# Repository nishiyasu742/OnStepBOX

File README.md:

# OnStepBOX

OnStepBOX is a compact, integrated controller box that combines an OnStep-compatible Smart Hand Controller (SHC) and the main OnStep controller into a single unit.  
This project is based on the **OnStep MaxESP3 hardware design** and uses the **OnStep firmware (GPLv3 licensed)**.  

---

## Overview

- **Purpose**: Simplify telescope control by merging two devices (main OnStep controller + SHC) into one.  
- **Base design**: Derived from the [OnStep MaxESP3](https://onstep.groups.io/g/main/wiki/MaxESP3) hardware.  
- **Firmware**: Fully compatible with OnStep firmware (licensed under GPLv3).  
- **Use case**: Ideal for amateur astronomers who want a reliable, compact, and user-friendly OnStep system without carrying multiple devices.  

---

## Features

- Integrated SHC and OnStep controller in a single enclosure  
- Based on the proven **OnStep MaxESP3 circuit design**  
- Compatible with the official OnStep firmware (GPLv3)    
- Compact build using an off-the-shelf plastic enclosure (machined, not 3D-printed)  
- Designed for DIY assembly with widely available components  

---

## Photos

- Image captured using a Takahashi EM200 mount.  

- OnStepBOX's appearance  

- The bottom surface of OnStepBOX  

- Inside the OnStepBOX  

---

## Schematic & Pin Mapping

This project follows the **OnStep MaxESP3** pin mapping for firmware configuration.  
Be sure to select the correct board definition in OnStep when compiling.  

- Schematic:  

---

## Required Components

- ESP32 development board (ESP-32S recommended)  
- Stepper motor drivers (e.g., DRV8825, TMC5160)  
- Standard OnStep-compatible connectors and cables  
- Off-the-shelf plastic enclosure (Takachi LC135-H-N-W)  
- Miscellaneous components (buttons, display, etc.)  

---

## Assembly Instructions

- **Prepare the enclosure**  
  Purchase the specified case (Takachi LC135-H-N-W)  and machine openings for connectors, display, and buttons using the attached G-code with a CNC milling machine.

- **Prepare the PCB**  
  Send the attached Gerber files to a PCB manufacturer (e.g., Elecrow, JLCPCB) and place an order.

- **Assemble the PCB**  
  Purchase the required components and solder them to complete the PCB.

- **Flash the firmware**  
  - Download the latest OnStep firmware.  
  - Flash the first MPU following the MaxESP3 pin map.  
  - Flash the second MPU with the Smart Hand Controller firmware.  

- **Final checks**  
  - Verify motor wiring and operation.  
  - Test the SHC interface.  
  - Confirm alignment and control with the telescope mount.  
---

## License

This project is distributed under the **GNU General Public License v3 (GPLv3)**.  
Since it is derived from **OnStep hardware and firmware**, it must remain open source.  

- A full copy of the GPLv3 license text is included in the [LICENSE](LICENSE) file.  

---

## Acknowledgments

- Original [OnStep project](https://onstep.groups.io/g/main) by **Howard Dutton** and contributors  
- OnStep MaxESP3 hardware design (the base for this project)  
- Open-source astronomy community for valuable feedback and improvements  

---

— NEWEVI

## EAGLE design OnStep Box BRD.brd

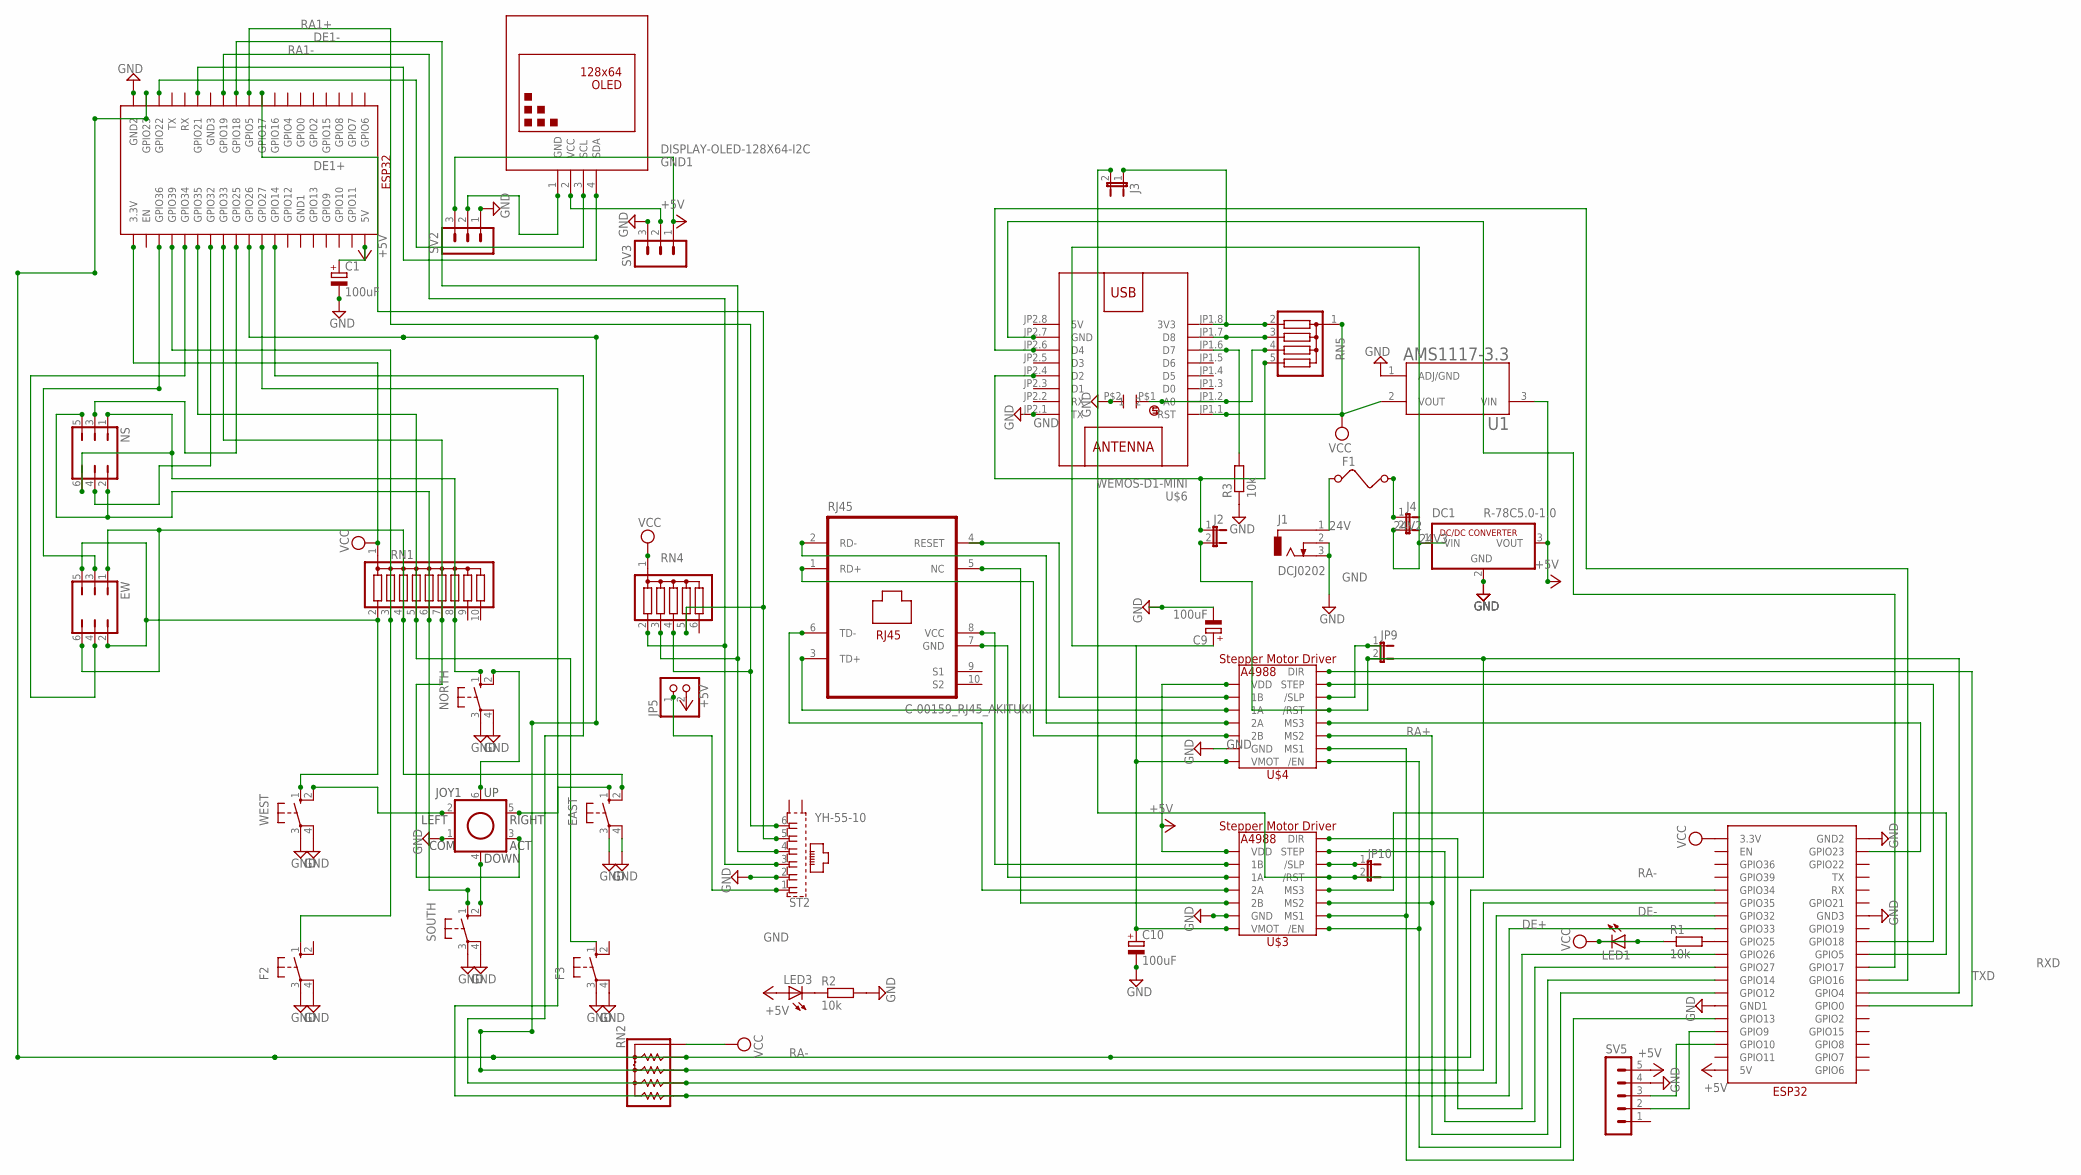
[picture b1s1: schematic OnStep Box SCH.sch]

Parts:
C1: 100uF; E2-4
C9, C10: 100uF; E2-5
CERAMIC_CAPACITOR1: CERAMIC_CAPACITOR
DC1: R-78C5.0-1.0; SIP3
EAST: 40-XX; B3F-40XX
EW: JP3Q
F1: FUSE
F2, F3: 10-XX; B3F-10XX
GND1: DISPLAY-OLED-128X64-I2C
J1: DCJ0202
J2, J3, J4: JP1E; JP1
JOY1: JOYSTICK
JP5: PINHD-1X2; 1X02
JP9, JP10: JP1E; JP1
LED1, LED3: LEDSFH480; SFH480
NORTH: 40-XX; B3F-40XX
NS: JP3Q
R1, R2, R3: 10k; 0204/5
RJ45: C-00159_RJ45_AKITUKI; PJ-J0
RN1: G09R; SIL10
RN2: 4605X; SIP5
RN4: G05R; SIL6
RN5: G04R; SIL5
SOUTH: 40-XX; B3F-40XX
ST2: YH-55-10
SV2, SV3: MA03-1
SV5: MA05-1
U1: AMS1117-3.3; SOT229P700X180-4N
U$1, U$7: ESP32
U$3, U$4: A4988_STEP
U$6: WEMOS-D1-MINI
WEST: 40-XX; B3F-40XX

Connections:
5V: U$6.JP2.8 (5V)
24V: F1.1, J1.1
24V2: F1.2, J4.1
24V3: C9.+, C10.+, DC1.1 (VIN), J4.2, U$3.VMOT, U$4.VMOT
+5V: C1.+, DC1.3 (VOUT), JP5.2, LED3.A, SV2.3, SV3.1, SV5.5, U1.3 (VIN), U$1.5V, U$3.VDD, U$4.VDD, U$7.5V
DE1+: RN4.5, ST2.5, U$7.GPIO17
DE1-: RN4.3, ST2.4, U$7.GPIO18
DE+: RN2.5, U$1.GPIO33, U$7.GPIO27
DE-: RN2.4, U$1.GPIO32, U$7.GPIO14
GND: C1.-, C9.-, C10.-, CERAMIC_CAPACITOR1.P$2 (2), DC1.2 (GND), EAST.3, EAST.4 (P1), F2.3, F2.4 (P1), F3.3, F3.4 (P1), J1.2, J1.3, JOY1.1 (COM), NORTH.3, NORTH.4 (P1), R2.2, R3.1, SOUTH.3, SOUTH.4 (P1), ST2.2, SV2.1, SV3.3, SV5.4, U1.1 (ADJ/GND), U$1.GND1, U$1.GND2, U$1.GND3, U$3.GND, U$3.GND2 (GND), U$4.GND, U$4.GND2 (GND), U$6.JP2.1 (TX), U$7.GND2, WEST.3, WEST.4 (P1)
unnamed: GND1.1 (GND), SV2.2
unnamed: LED3.K (C), R2.1
unnamed: R1.2, U$1.GPIO25
unnamed: SV5.3, U$1.GPIO10
unnamed: SV5.2, U$1.GPIO9
unnamed: U$1.GPIO12, U$3./EN, U$4./EN
unnamed: U$1.GPIO13, U$3.MS1, U$4.MS1
unnamed: U$1.GPIO14, U$3.MS2, U$4.MS2
unnamed: JP10.1, U$3./SLP
unnamed: U$1.GPIO26, U$3.DIR
unnamed: U$1.GPIO27, U$3.STEP
unnamed: U$1.GPIO23, U$4.MS3
unnamed: J2.2, J3.2, JP9.1, JP9.2, JP10.2, U$1.GPIO4, U$3./RST, U$4./RST, U$4./SLP
unnamed: J3.1, RN5.2, U$6.JP1.8 (3V3)
unnamed: U$1.GPIO18, U$4.STEP
unnamed: RJ45.4 (RESET), U$4.1B
unnamed: RJ45.5 (NC), U$3.2B
unnamed: RJ45.8 (VCC), U$3.1B
unnamed: GND1.2 (VCC), SV3.2
unnamed: RJ45.7 (GND), U$3.1A
unnamed: RN5.3, U$6.JP1.7 (D8)
unnamed: RJ45.6 (TD-), U$3.2A
unnamed: U$1.GPIO5, U$3.MS3
unnamed: R3.2, U$6.JP1.6 (D7)
unnamed: CERAMIC_CAPACITOR1.P$1 (1), RN5.4, U$6.JP1.2 (A0)
unnamed: U$1.GPIO0, U$4.DIR
unnamed: RJ45.2 (RD-), U$4.2A
unnamed: RJ45.1 (RD+), U$4.2B
unnamed: J2.1, RN5.5, U$6.JP2.4 (D2)
unnamed: RJ45.3 (TD+), U$4.1A
unnamed: GND1.3 (SCL), U$7.GPIO22
unnamed: GND1.4 (SDA), U$7.GPIO21
unnamed: EW.3, U$7.GPIO36
unnamed: EAST.2 (S1), EW.1, EW.6, RN1.4
unnamed: NS.2, NS.5, RN1.6, SOUTH.1 (S)
unnamed: JOY1.2 (LEFT), WEST.2 (S1)
unnamed: EAST.1 (S), JOY1.5 (RIGHT)
unnamed: NORTH.1 (S), NS.1, NS.6, RN1.8
unnamed: JP5.1, ST2.1
unnamed: F2.1 (S), RN1.3, U$7.GPIO39
unnamed: F3.1 (S), RN1.5, U$7.GPIO35
unnamed: NS.3, U$7.GPIO25
unnamed: NS.4, U$7.GPIO32
unnamed: EW.2, EW.5, RN1.2, WEST.1 (S)
unnamed: EW.4, U$7.GPIO34
unnamed: JOY1.6 (UP), NORTH.2 (S1)
unnamed: JOY1.4 (DOWN), SOUTH.2 (S1)
unnamed: JOY1.3 (ACT), RN1.7, U$7.GPIO33
RA1+: RN4.4, ST2.6, U$7.GPIO5
RA1-: RN4.2, ST2.3, U$7.GPIO19
RA+: RN2.3, U$1.GPIO35, U$7.GPIO26
RA-: RN2.2, U$1.GPIO34, U$7.GPIO23
RXD: U$1.GPIO17, U$6.JP2.7 (GND)
TXD: U$1.GPIO16, U$6.JP2.6 (D4)
VCC: LED1.A, LED1.K (C), R1.1, RN1.1, RN2.1, RN4.1, RN5.1, U1.2 (VOUT), U$1.3.3V, U$6.JP1.1 (RST), U$7.3.3V

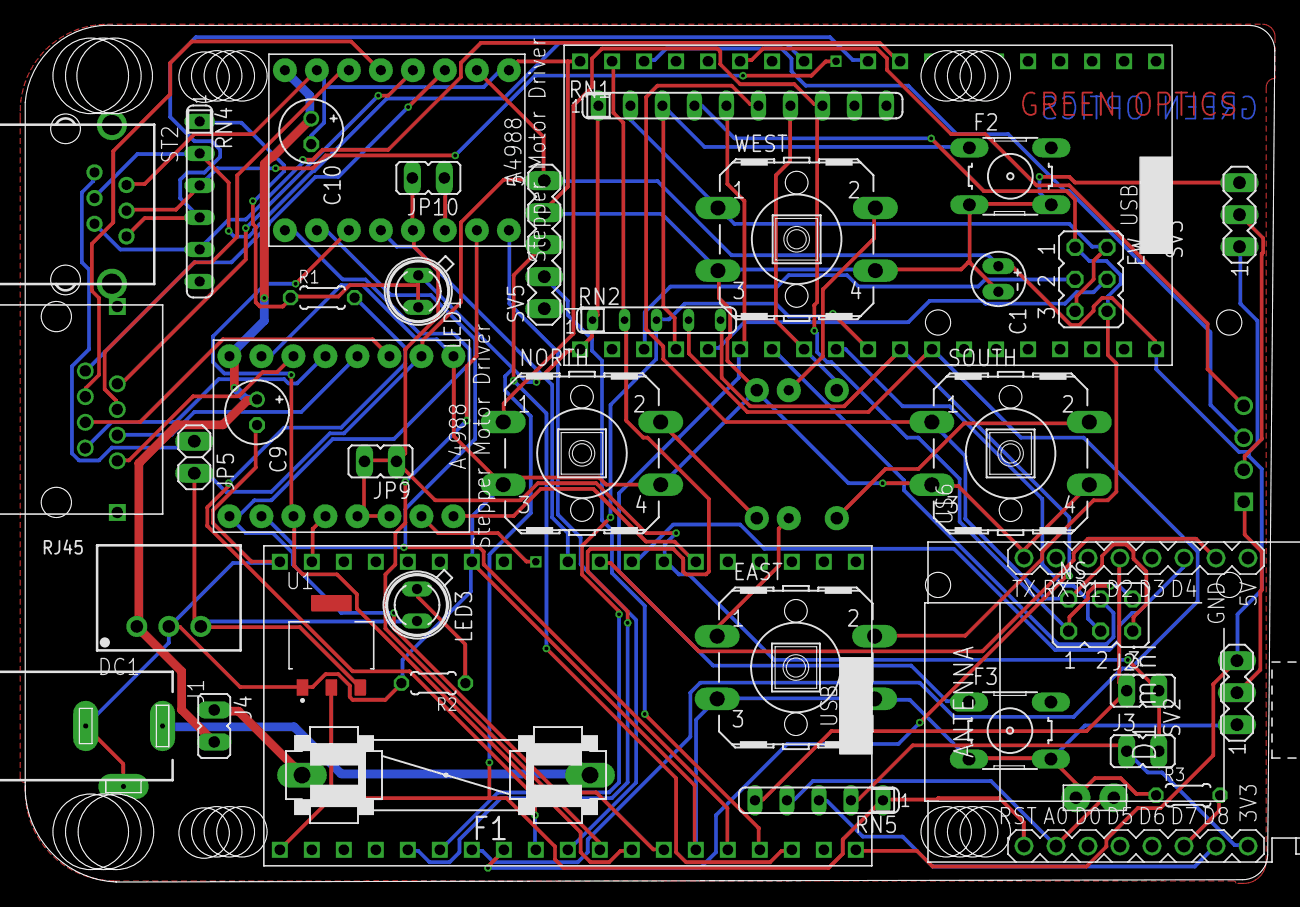
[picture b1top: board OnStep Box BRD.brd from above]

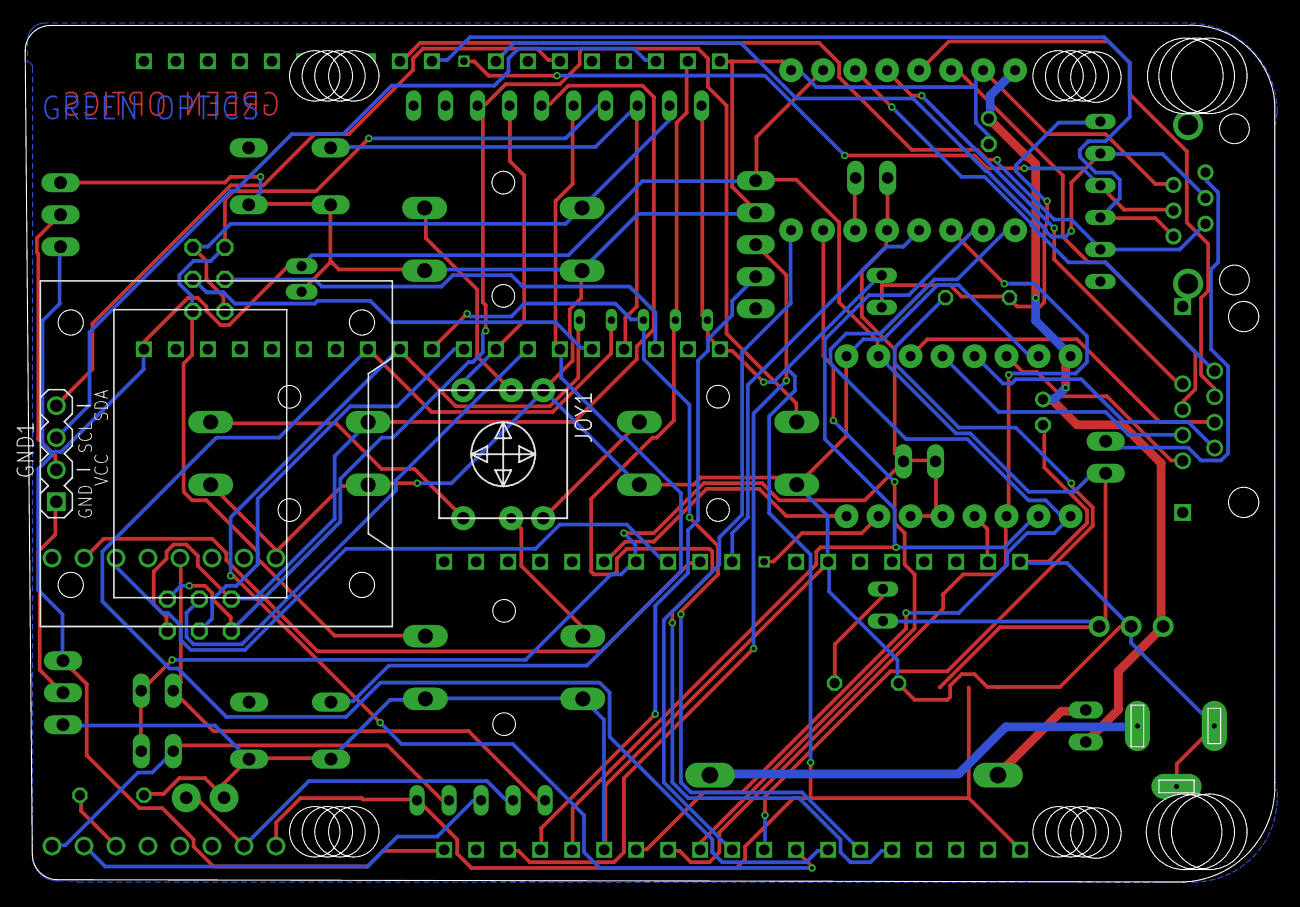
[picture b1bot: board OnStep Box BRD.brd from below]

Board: 2 copper layers, 99.2 x 68.0 mm, 43 parts (2 on the bottom side), 64 nets.

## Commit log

2025-09-06 Update README.md
    Update README.md with new content
2025-09-06 Update README.md
    回路図の追加
2025-09-06 Create LICENSE

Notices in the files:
parts and their libraries:
diy-modules: Released under the Creative Commons Attribution 4.0 International License: http://creativecommons.org/licenses/by/4.0
